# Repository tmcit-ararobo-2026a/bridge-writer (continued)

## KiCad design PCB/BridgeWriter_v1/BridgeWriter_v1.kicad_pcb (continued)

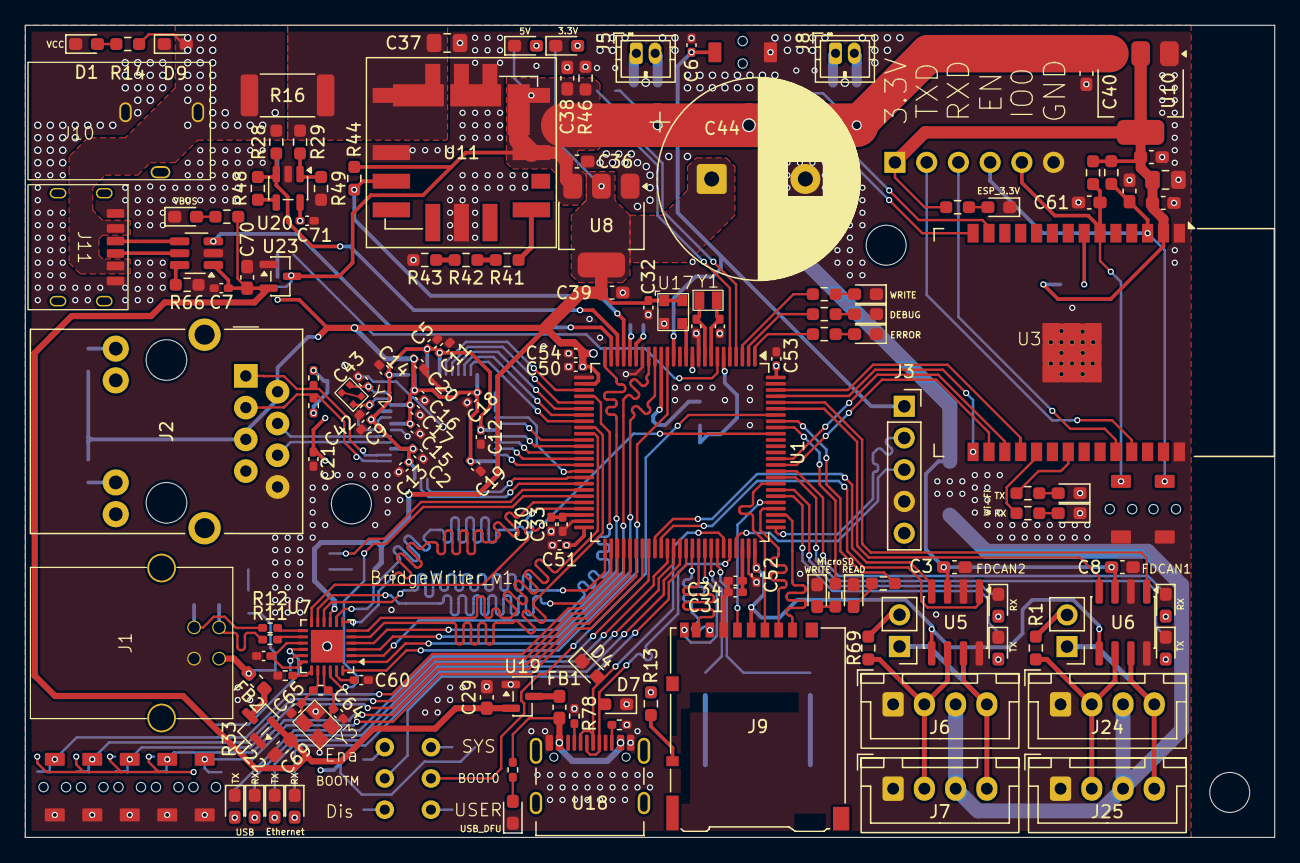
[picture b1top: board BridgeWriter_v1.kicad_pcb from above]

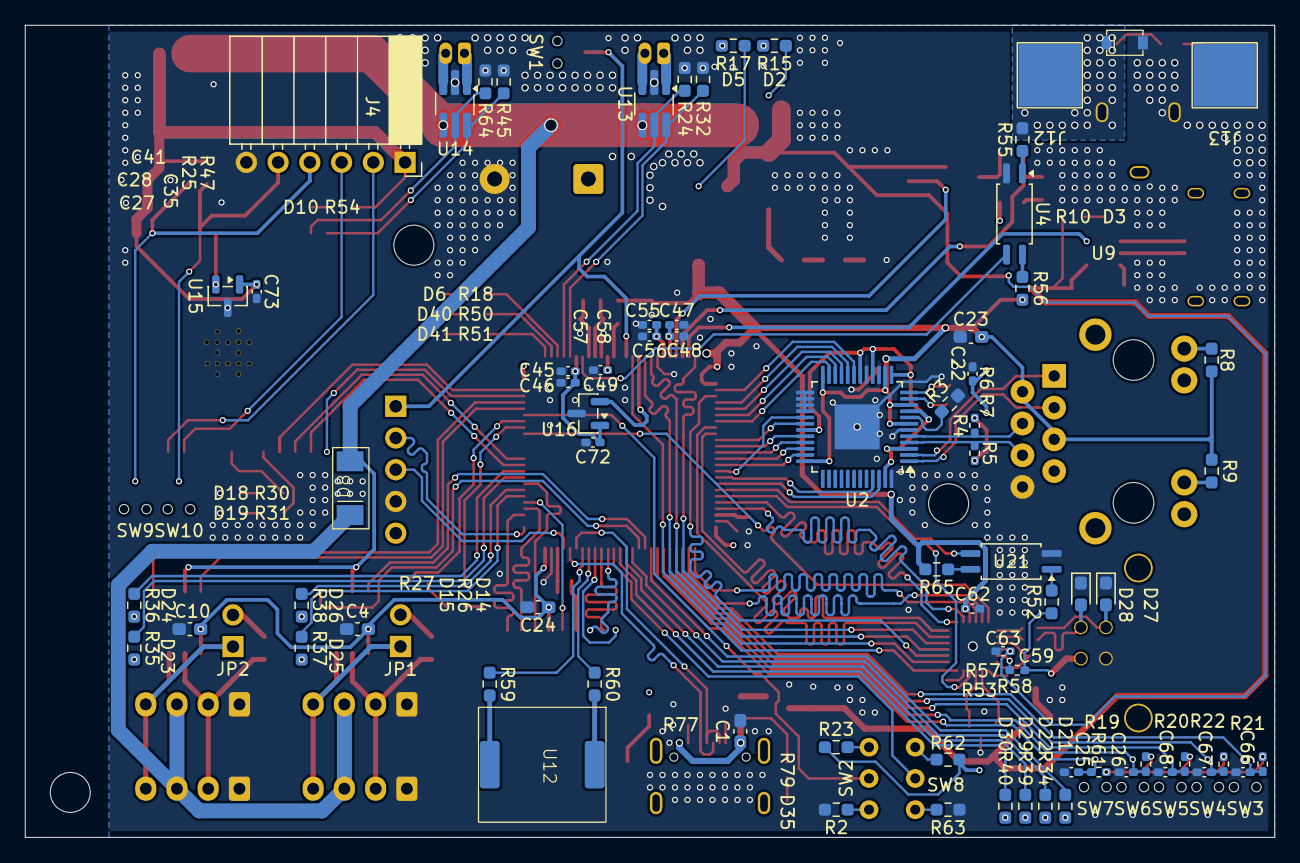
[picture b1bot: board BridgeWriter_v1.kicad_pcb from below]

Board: 4 copper layers, 100.0 x 65.0 mm, 229 parts (72 on the bottom side), 176 nets.

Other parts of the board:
H2, H2#2, H2#3: MountingHole; MountingHole_3.2mm_M3

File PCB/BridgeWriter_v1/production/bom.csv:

Designator,Footprint,Quantity,Value,LCSC Part #
C1,0603,1,0.01uF,
"C10, C23, C24, C27, C29, C3, C35, C4, C61, C69, C70, C8",0603,12,0.1uF,
"C11, C12, C13, C14, C15, C16, C17, C18, C19, C2, C21, C22, C25, C26, C32, C33, C34, C45, C48, C49, C5, C50, C51, C52, C53, C56, C59, C6, C60, C62, C63, C66, C67, C68, C71, C72, C73, C9",0402,38,0.1uF,
"C20, C46, C47, C55, C7",0402,5,1uF,
"C28, C37",0805,2,22uF,
"C30, C31",0402,2,2.2uF,
"C36, C39, C40, C41",0603,4,1uF,
C38,0603,1,10uF,
"C42, C43, C64, C65",0402,4,3pF,
C44,CP_Radial_D16.0mm_P7.50mm,1,4700uF,
C54,0402,1,4.7uF,
"C57, C58",0402,2,8pF,
"D1, D10, D2, D3, D5",0603,5,W,
D13,SS2040FL,1,SS2040FL,
"D14, D18, D21, D23, D25, D29, D40",0603,7,B,
"D15, D19, D22, D24, D26, D30",0603,6,G,
"D27, D28, D4, D7, D9",0603,5,ESD,
D35,0603,1,LED,
D41,0603,1,R,
D6,0603,1,O,
D8,SB34AFC,1,SB34AFC,
"FB1, FB2",0603,2,600Ω/500mA,
"H2_3, H2_2, H2",MountingHole_3.2mm_M3,3,MountingHole,
J1,USB-4BF-103BS,1,USB_B,
J10,DC_Jack_18742,1,Barrel_Jack_MountingPin,
J11,632722100213,1,USB_C_Receptacle_PowerOnly_6P,
"J12, J13",5x5,2,Conn_01x01,
J2,RJ45_Bel_SI-60062-F,1,RJ45_Bel_SI-60062-F,
"J24, J25, J6, J7",JST_XH_B4B-XH-A_1x04_P2.50mm_Vertical,4,Conn_01x04,
J3,PinSocket_1x05_P2.54mm_Vertical,1,Conn_01x05,
J4,PinSocket_1x06_P2.54mm_Horizontal,1,Conn_01x06,
"J5, J8",JST_ZH_B2B-ZR_1x02_P1.50mm_Vertical,2,Conn_01x02,
J9,microSD_HC_Hirose_DM3AT-SF-PEJM5,1,Micro_SD_Card_Det2,
"JP1, JP2",PinHeader_1x02_P2.54mm_Vertical,2,Jumper_2_Bridged,
"R1, R69",0603,2,120,
"R10, R13, R14, R15, R17, R18, R23, R24, R25, R26, R27, R30, R31, R32, R33, R34, R35, R36, R37, R38, R39, R40, R41, R45, R47, R50, R51, R54, R56, R62, R64, R65",0603,32,1k,
"R11, R12",0402,2,22,
R16,2512,1,1mΩ,
"R19, R20, R21, R22, R61",0402,5,1k,
"R2, R52, R55, R63",0603,4,10k,
"R28, R29",0603,2,100,
R3,0603,1,12.3k,
"R4, R5, R6, R7",0402,4,46.9k,
"R42, R59, R60, R8, R9",0603,5,330,
R43,0603,1,10,
R44,0603,1,100k,
R46,0603,1,1.2k,
"R48, R49",0603,2,50k,
R53,0402,1,1M,
R57,0402,1,20k,
R58,0402,1,8.06k,
R66,0603,1,24k,
"R77, R78",0402,2,4.7kΩ,
R79,0402,1,1kΩ,
"SW1, SW10, SW3, SW4, SW5, SW6, SW7, SW9",switch_TVAF06-A020B-R,8,SW_Push,
SW2,swich_SS-12D00G3,1,BOOT_MODE0,
SW8,swich_SS-12D00G3,1,BOOT_MODE1,
U1,LQFP-100_14x14mm_P0.5mm,1,STM32H723VGTx,
"U10, U8",SOT-223-3_TabPin2,2,TPS1117LV33S,
U11,OKL_T6_W12,1,OKL-T/6-W12N-C,
U12,PT86-091940LMR,1,PT86-091940LMR,
"U13, U14",TSOT-23-6_HandSoldering,2,AM8068,
"U15, U16",SOT-23,2,MCP9700x-ETT,
U17,ECS-TXO-2520-33-500-AN-TR,1,~,
U18,USB_C_Receptacle_Nelton_5077CR-16-SMC2-BK-TR,1,USB_Type-C,
"U19, U22, U23",SOT-23,3,CH213K,
U2,LQFP-48-1EP_7x7mm_P0.5mm_EP3.6x3.6mm,1,W6300,
U20,SOT-23-5,1,KIA75S358F,
"U21, U4",SOIC-4_4.55x2.6mm_P1.27mm,2,TLP293,
U3,ESP32-C5-WROOM-1,1,ESP32-C5-WROOM-1,
"U5, U6",SOIC-8_3.9x4.9mm_P1.27mm,2,MCP2562-E-SN,
U7,QFN-24-1EP_4x4mm_P0.5mm_EP2.6x2.6mm,1,USB3343,
U9,SOT-23-6_Handsoldering,1,CH221K,
Y1,FC2012SN 32.768K-70NNA0KC0,1,FC2012SN 32.768K-70NNA0KC0,
Y2,XRCGB25M000FFS1AR0,1,XRCGB25M000FFS1AR0,
Y3,ECS-600-8-36B-CTN-TR,1,ECS-600-8-36B-CTN-TR,

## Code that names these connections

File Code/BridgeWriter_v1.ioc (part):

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Mcu.Name=STM32H723VGTx
Mcu.Package=LQFP100
Mcu.UserName=STM32H723VGTx
PA0.GPIOParameters=GPIO_Label
PA0.GPIO_Label=PGOOD
PA0.Signal=GPIO_Input
PA1.GPIOParameters=GPIO_Label
PA1.GPIO_Label=POWER_MONITOR
PA1.Mode=IN17-Single-Ended
PA1.Signal=ADC1_INP17
PA10.GPIOParameters=GPIO_Speed,GPIO_Label
PA10.GPIO_Label=Speaker_IN2
PA10.GPIO_Speed=GPIO_SPEED_FREQ_MEDIUM
PA10.Signal=S_TIM1_CH3
PA13(JTMS/SWDIO).Mode=Serial_Wire
PA13(JTMS/SWDIO).Signal=DEBUG_JTMS-SWDIO
PA14(JTCK/SWCLK).Mode=Serial_Wire
PA14(JTCK/SWCLK).Signal=DEBUG_JTCK-SWCLK
PA2.GPIOParameters=GPIO_Label
PA2.GPIO_Label=USB_PD_GOOD
PA2.Signal=GPIO_Input
PA3.Mode=Device_HS
PA3.Signal=USB_OTG_HS_ULPI_D0
PA4.GPIOParameters=GPIO_Label
PA4.GPIO_Label=W6300_LNK
PA4.Signal=GPIO_Input
PA5.Mode=Device_HS
PA5.Signal=USB_OTG_HS_ULPI_CK
PA6.GPIOParameters=GPIO_Label
PA6.GPIO_Label=W6300_SPD
PA6.Signal=GPIO_Input
PA7.GPIOParameters=GPIO_Label
PA7.GPIO_Label=W6300_DPXn
PA7.Signal=GPIO_Input
PA8.GPIOParameters=GPIO_Label
PA8.GPIO_Label=SDMMC_CHECK
PA8.Signal=GPIO_Input
PA9.GPIOParameters=GPIO_Speed,GPIO_Label
PA9.GPIO_Label=Speaker_IN1
PA9.GPIO_Speed=GPIO_SPEED_FREQ_MEDIUM
PA9.Signal=S_TIM1_CH2
PB0.Mode=Device_HS
PB0.Signal=USB_OTG_HS_ULPI_D1
PB1.Mode=Device_HS
PB1.Signal=USB_OTG_HS_ULPI_D2
PB10.Mode=Device_HS
PB10.Signal=USB_OTG_HS_ULPI_D3
PB11.Mode=Device_HS
PB11.Signal=USB_OTG_HS_ULPI_D4
PB12.Mode=Device_HS
PB12.Signal=USB_OTG_HS_ULPI_D5
PB13.Mode=Device_HS
PB13.Signal=USB_OTG_HS_ULPI_D6
PB14.GPIOParameters=GPIO_Label
PB14.GPIO_Label=FDCAN1_RESET
PB14.Signal=GPIO_Input
PB15.GPIOParameters=GPIO_Label
PB15.GPIO_Label=FDCAN2_RESET
PB15.Signal=GPIO_Input
PB2.Mode=O1_P1_CLK
PB2.Signal=OCTOSPIM_P1_CLK
PB5.Mode=Device_HS
PB5.Signal=USB_OTG_HS_ULPI_D7
PB6.GPIOParameters=GPIO_Label
PB6.GPIO_Label=SDMMC_WRITE_LED
PB6.Signal=GPIO_Output
PB7.GPIOParameters=GPIO_Label
PB7.GPIO_Label=SDMMC_READ_LED
PB7.Signal=GPIO_Output
PB8.Mode=FDCAN_Activate
PB8.Signal=FDCAN1_RX
PB9.Mode=FDCAN_Activate
PB9.Signal=FDCAN1_TX
PC0.Mode=Device_HS
PC0.Signal=USB_OTG_HS_ULPI_STP
PC1.Signal=ADCx_INP11
PC10.Mode=SD_4_bits_Wide_bus
PC10.Signal=SDMMC1_D2
PC11.Mode=SD_4_bits_Wide_bus
PC11.Signal=SDMMC1_D3
PC12.Mode=SD_4_bits_Wide_bus
PC12.Signal=SDMMC1_CK
PC13.GPIOParameters=GPIO_Label
PC13.GPIO_Label=POWER_MONITOR
PC13.Signal=GPIO_Input
PC14-OSC32_IN.Mode=LSE-External-Oscillator
PC14-OSC32_IN.Signal=RCC_OSC32_IN
PC15-OSC32_OUT.Mode=LSE-External-Oscillator
PC15-OSC32_OUT.Signal=RCC_OSC32_OUT
PC2_C.Mode=Device_HS
PC2_C.Signal=USB_OTG_HS_ULPI_DIR
PC3_C.Mode=Device_HS
PC3_C.Signal=USB_OTG_HS_ULPI_NXT
PC4.GPIOParameters=GPIO_Label,GPIO_ModeDefaultEXTI
PC4.GPIO_Label=W6300_ACT
PC4.GPIO_ModeDefaultEXTI=GPIO_MODE_IT_RISING_FALLING
PC4.Signal=GPXTI4
PC5.GPIOParameters=GPIO_Label
PC5.GPIO_Label=W6300_COL
PC5.Signal=GPXTI5
PC6.GPIOParameters=GPIO_Label
PC6.GPIO_Label=Ethernet_RX_LED
PC6.Signal=GPIO_Output
PC7.GPIOParameters=GPIO_Label
PC7.GPIO_Label=BOOTMODE
PC7.Signal=GPIO_Input
PC8.Mode=SD_4_bits_Wide_bus
PC8.Signal=SDMMC1_D0
PC9.Mode=SD_4_bits_Wide_bus
PC9.Signal=SDMMC1_D1
PD0.GPIOParameters=GPIO_Label
PD0.GPIO_Label=FDCAN2_TX_LED
PD0.Signal=GPIO_Output
PD1.GPIOParameters=GPIO_Label
PD1.GPIO_Label=FDCAN2_RX_LED
PD1.Signal=GPIO_Output
PD10.GPIOParameters=GPIO_Label
PD10.GPIO_Label=Wi-Fi_RESET
PD10.Signal=GPIO_Input
PD11.GPIOParameters=GPIO_Label
PD11.GPIO_Label=USB_TX_LED
PD11.Signal=GPIO_Output
PD12.Mode=FDCAN_Activate
PD12.Signal=FDCAN3_RX
PD13.Mode=FDCAN_Activate
PD13.Signal=FDCAN3_TX
PD14.GPIOParameters=GPIO_Label
PD14.GPIO_Label=USB_RX_LED
PD14.Signal=GPIO_Output
PD15.GPIOParameters=GPIO_Label
PD15.GPIO_Label=Ethernet_TX_LED
PD15.Signal=GPIO_Output
PD2.Mode=SD_4_bits_Wide_bus
PD2.Signal=SDMMC1_CMD
PD3.GPIOParameters=GPIO_Label
PD3.GPIO_Label=FDCAN1_TX_LED
PD3.Signal=GPIO_Output
PD4.GPIOParameters=GPIO_Label
PD4.GPIO_Label=FDCAN1_RX_LED
PD4.Signal=GPIO_Output
PD5.Mode=Asynchronous
PD5.Signal=USART2_TX
PD6.Mode=Asynchronous
PD6.Signal=USART2_RX
PD8.GPIOParameters=GPIO_Label
PD8.GPIO_Label=Ethernet_RESET
PD8.Signal=GPIO_Input
PD9.GPIOParameters=GPIO_Label
PD9.GPIO_Label=USB_RESET
PD9.Signal=GPIO_Input
PE0.GPIOParameters=GPIO_Speed,GPIO_Label
PE0.GPIO_Label=FW_UART_TXF
PE0.GPIO_Speed=GPIO_SPEED_FREQ_VERY_HIGH
PE0.Signal=GPIO_Output
PE1.GPIOParameters=GPIO_Label
PE1.GPIO_Label=FW_UART_RXF
PE1.Signal=GPIO_Input
PE10.Mode=OCTOSPI1_IOL_Port1H
PE10.Signal=OCTOSPIM_P1_IO7
PE11.Mode=OCTOSPI1_Port1_NCS
PE11.Signal=OCTOSPIM_P1_NCS
PE12.GPIOParameters=GPIO_Label,GPIO_ModeDefaultEXTI
PE12.GPIO_Label=W6300_INT
PE12.GPIO_ModeDefaultEXTI=GPIO_MODE_IT_RISING_FALLING
PE12.Signal=GPXTI12
PE13.GPIOParameters=GPIO_Speed,GPIO_Label
PE13.GPIO_Label=W6300_RST
PE13.GPIO_Speed=GPIO_SPEED_FREQ_VERY_HIGH
PE13.Signal=GPIO_Output
PE14.GPIOParameters=GPIO_Label
PE14.GPIO_Label=USB_HS_CHECK
PE14.Signal=GPIO_Input
PE15.GPIOParameters=GPIO_Speed,GPIO_Label
PE15.GPIO_Label=USB3343_RST
PE15.GPIO_Speed=GPIO_SPEED_FREQ_VERY_HIGH
PE15.Signal=GPIO_Output
PE2.GPIOParameters=GPIO_Label
PE2.GPIO_Label=ERROR_LED
PE2.Signal=GPIO_Output
PE3.GPIOParameters=GPIO_Label
PE3.GPIO_Label=DEBUG_LED
PE3.Signal=GPIO_Output
PE4.GPIOParameters=GPIO_Label
PE4.GPIO_Label=WRITE_MODE_LED
PE4.Signal=GPIO_Output
PE5.GPIOParameters=GPIO_Speed,GPIO_Label
PE5.GPIO_Label=FAN_INB
PE5.GPIO_Speed=GPIO_SPEED_FREQ_MEDIUM
PE5.Signal=S_TIM15_CH1
PE6.GPIOParameters=GPIO_Speed,GPIO_Label
PE6.GPIO_Label=FAN_INA
PE6.GPIO_Speed=GPIO_SPEED_FREQ_MEDIUM
PE6.Signal=S_TIM15_CH2
PE7.Mode=OCTOSPI1_IOL_Port1H
PE7.Signal=OCTOSPIM_P1_IO4
PE8.Mode=OCTOSPI1_IOL_Port1H
PE8.Signal=OCTOSPIM_P1_IO5
PE9.Mode=OCTOSPI1_IOL_Port1H
PE9.Signal=OCTOSPIM_P1_IO6
PH0-OSC_IN.Mode=HSE-External-Clock-Source
PH0-OSC_IN.Signal=RCC_OSC_IN
RCC.HSE_VALUE=50000000
RCC.SYSCLKFreq_VALUE=550000000
RCC.SYSCLKSource=RCC_SYSCLKSOURCE_PLLCLK
board=custom

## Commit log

2026-03-08 add README
2026-03-08 add first bootloader image
2026-03-15 add ESP32_UART and creatting PCB
2026-03-16 Update Wi-Fi support from Wi-Fi4 to Wi-Fi6
2026-03-16 change
2026-03-17 Update Wi-Fi interface version in README
2026-03-17 Fix formatting in README for interface support section
2026-03-17 All the wiring except the power is probably done.
2026-03-18 Completed PCB
2026-03-19 基盤でdfu機能使えるけど肝心のusbつけてなかった
2026-03-19 DFUのType-C追加 FDCANのピン間違い修正 電源供給はUSB PDにしようかなと
2026-03-21 基板にTVSダイオードと逆接保護追加 給電をUSB PD かDC ジャックにしようと思う サージ電圧保護とOCPとOVPを追加する予定
2026-03-22 USB PD追加
2026-03-22 フォルダの作成
2026-03-22 app/cmakelistsの追加
2026-03-22 docs : PCB作成途中 書き込み基板のPCBを一から作り直し
2026-03-23 PCB電源LED以外配線終わり やること LED追加と、シルクの被り解消
2026-03-24 ほぼ完成
2026-03-24 PCB一応完成
2026-03-25 feat : GENERATE CODE fdcanクラスの作成
    ブランチの追加たがまだわかっていないので次回からブランチを使います。
2026-03-25 fix fdcan追加
2026-03-25 feat : timeoutと送信完了割り込みを追加
    ハードウェア側での受信タイムアウトの追加
    送信完了割り込みを追加
2026-03-25 branch test
2026-03-25 fdcan内のSend追加
2026-03-26 test
2026-03-26 delte test
2026-03-26 新しいfdacnクラスの作成９割完成
2026-03-26 PCB 変更シルクを少しつけた
2026-03-27 classic can fdcanの選択はありにする
2026-03-28 勝手に改行擦れてしまうのを解除
